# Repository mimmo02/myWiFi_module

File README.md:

# myWiFi_module

Generic WiFi pcb based on ESP12E module, with 6 output and 3 input.
Appropriate to develope IoT application.

## Authors

- [@Domenico Aquilino](https://github.com/mimmo02)

## Hardware

The IO are customizable, in this case the configuration is made such as there are 6 output and 3 input.

#### Mounted components:

| Component | Type     | Module ESP12E |
| :-------- | :------- | :------------------------- |
| `R6 & R13` | input | `GPIO16` |
| `R7 & R14` | input | `GPIO14` |
| `R8 & R15` | input | `GPIO12` |
| `Q4` | output | `GPIO13` |
| `Q5` | output | `GPIO15` |
| `Q6` | output | `GPIO02` |
| `Q7` | output | `GPIO00` |
| `Q8` | output | `GPIO04` |
| `Q9` | output | `GPIO05` |

#### PCB PIN:

alimentation jumper
| Connector | Pin     | Description |
| :-------- | :------ | :---------- |
| **JP1** | `1-4` | 24V |
| **JP1** | `2-5` | 5V |
| **JP1** | `3-6` | 3.3V |

alimentation connector
| Connector | Pin     | Description |
| :-------- | :------ | :---------- |
| **X1** | `1` | GND |
| **X1** | `2` | +24V |
| **X1** | `3` | +5V |
| **X1** | `4` | +3.3V |

programmation connector
| Connector | Pin     | Description |
| :-------- | :------ | :---------- |
| **X3** | `1` | Rx |
| **X3** | `2` | Tx |
| **X3** | `3` | GND |

GPIO connector
| Connector | Pin     | ESP12E |  esp8266 |
| :-------- | :------ | :---------- | :-----|
| **X2** | `1` | GND | GND |
| **X2** | `2` | GPIO16 | GPIO16 |
| **X2** | `3` | GPIO14 | GPIO14 |
| **X2** | `4` | GPIO12 | GPIO12 |
| **X2** | `5` | GPIO13 | GPIO13 |
| **X2** | `6` | GPIO15 | GPIO15 |
| **X2** | `7` | GPIO02 | GPIO02 |
| **X2** | `8` | GPIO00 | GPIO00 |
| **X2** | `9` | GPIO04 | GPIO04 |
| **X2** | `10` | GPIO05 | GPIO05 |
| **X2** | `11` | ADC | ADC |

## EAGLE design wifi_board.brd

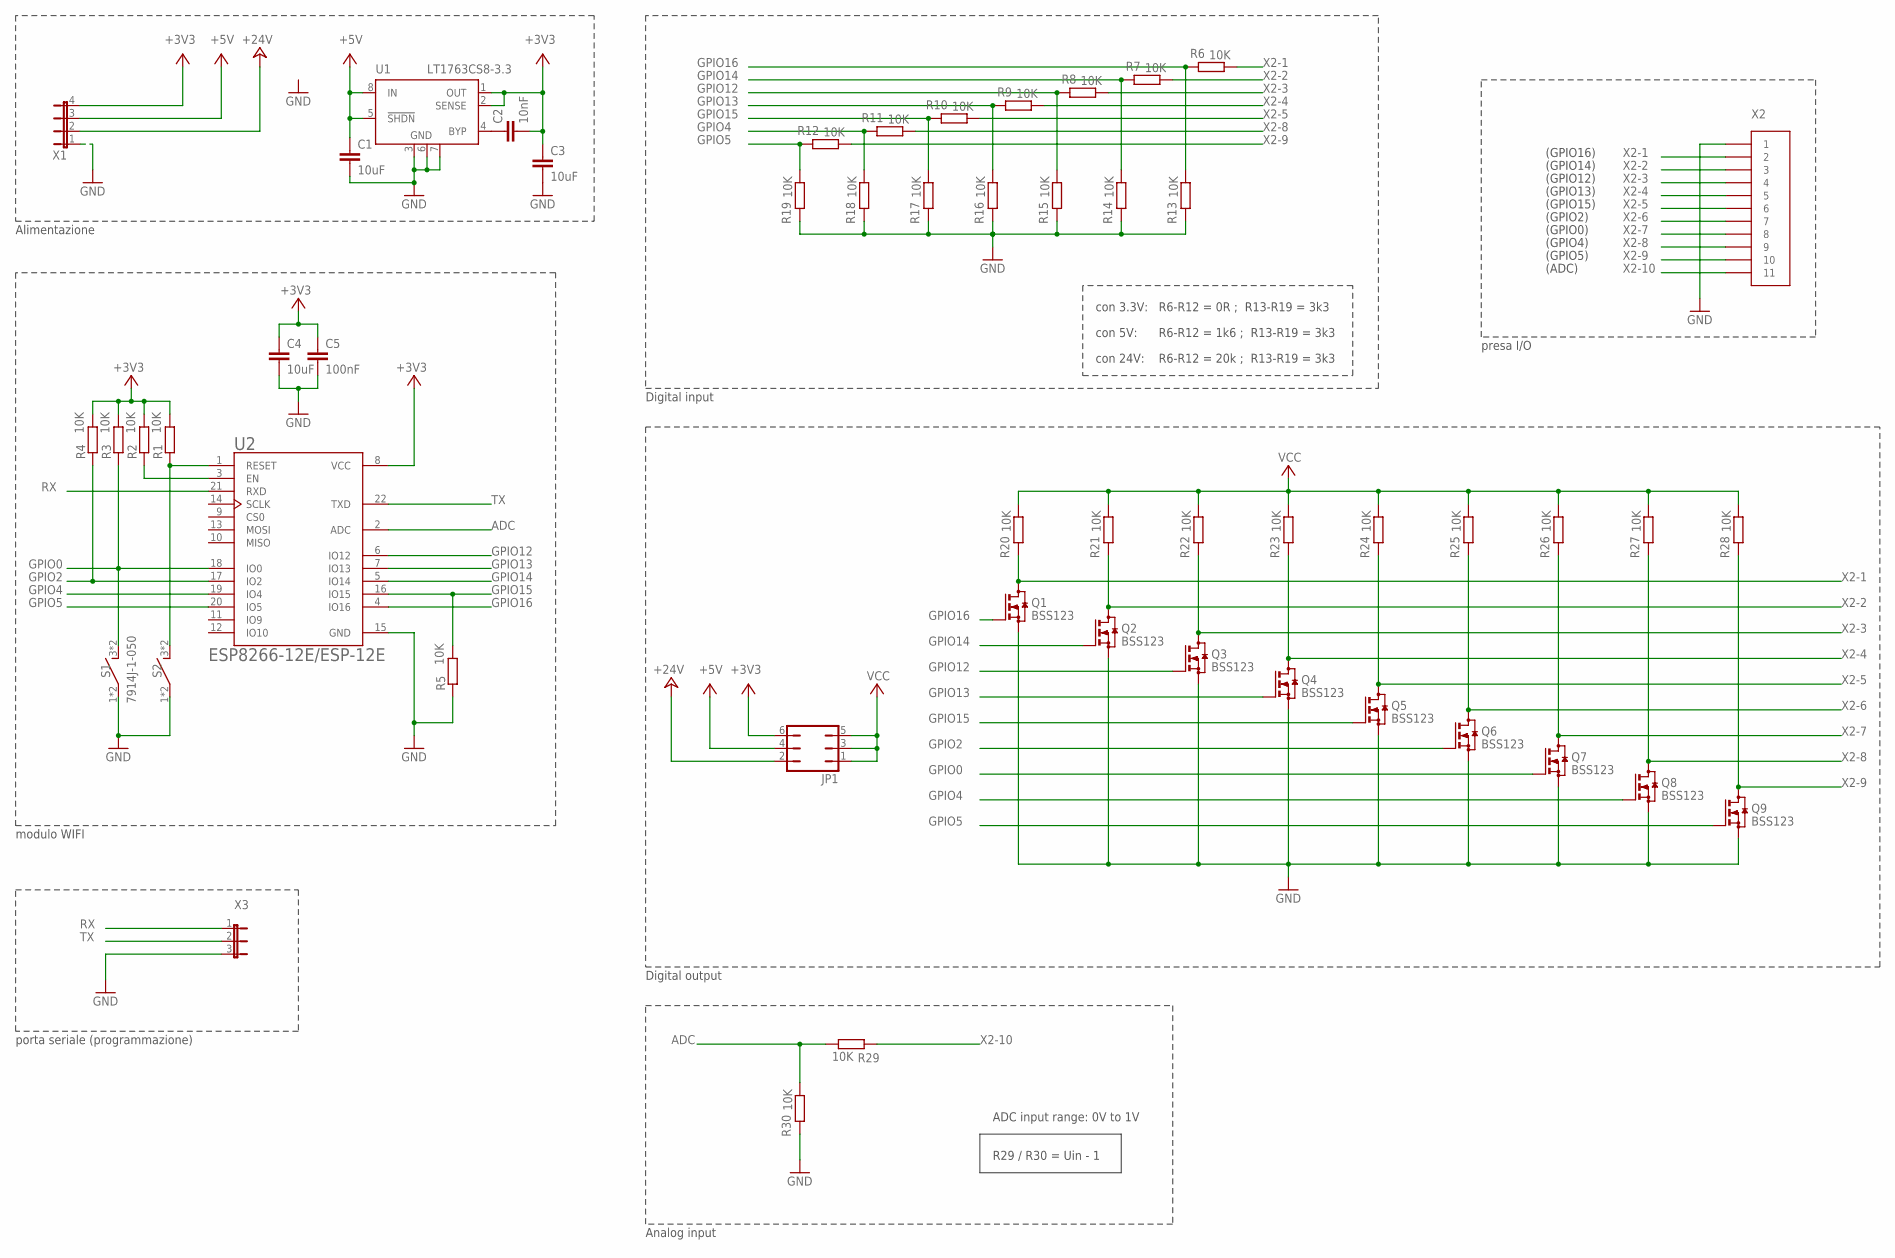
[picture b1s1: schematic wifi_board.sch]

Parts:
C1, C3, C4: 10uF; C0805
C2: 10nF; C0805
C5: 100nF; C0805
JP1: JP3Q
Q1, Q2, Q3, Q4, Q5, Q6, Q7, Q8, Q9: BSS123; SOT23
R1, R2, R3, R4, R5, R6, R7, R8, R9, R10, R11, R12, R13, R14, R15, R16, R17, R18, R19, R20, R21, R22, R23, R24, R25, R26, R27, R28, R29, R30: 10K; R0805
S1, S2: 7914J-1-050; 7914J1000E
U1: LT1763CS8-3.3; SOIC8
U2: ESP8266-12E/ESP-12E; XCVR_ESP8266-12E/ESP-12E
X1: JP4E; JP4
X2: X11P
X3: JP2E; JP2

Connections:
+3V3: C2.2, C3.1, C4.1, C5.1, JP1.6, R1.2, R2.2, R3.2, R4.2, U1.1 (OUT), U1.2 (SENSE), U2.8 (VCC), X1.4
+5V: C1.1, JP1.4, U1.5 (!SHDN), U1.8 (IN), X1.3
+24V: JP1.2, X1.2
ADC: R29.1, R30.1, U2.2 (ADC)
GND: C1.2, C3.2, C4.2, C5.2, Q1.2 (S), Q2.2 (S), Q3.2 (S), Q4.2 (S), Q5.2 (S), Q6.2 (S), Q7.2 (S), Q8.2 (S), Q9.2 (S), R5.1, R13.2, R14.2, R15.2, R16.2, R17.2, R18.2, R19.2, R30.2, S1.1, S1.2 (1), S2.1, S2.2 (1), U1.3 (GND), U1.6 (GND), U1.7 (GND), U2.15 (GND), X1.1, X2.1, X3.3
GPIO0: Q7.1 (G), R3.1, S1.3 (2), S1.4 (2), U2.18 (IO0)
GPIO2: Q6.1 (G), R4.1, U2.17 (IO2)
GPIO4: Q8.1 (G), R11.2, R18.1, U2.19 (IO4)
GPIO5: Q9.1 (G), R12.2, R19.1, U2.20 (IO5)
GPIO12: Q3.1 (G), R8.2, R15.1, U2.6 (IO12)
GPIO13: Q4.1 (G), R9.2, R16.1, U2.7 (IO13)
GPIO14: Q2.1 (G), R7.2, R14.1, U2.5 (IO14)
GPIO15: Q5.1 (G), R5.2, R10.2, R17.1, U2.16 (IO15)
GPIO16: Q1.1 (G), R6.2, R13.1, U2.4 (IO16)
unnamed: R1.1, S2.3 (2), S2.4 (2), U2.1 (RESET)
unnamed: R2.1, U2.3 (EN)
unnamed: C2.1, U1.4 (BYP)
RX: U2.21 (RXD), X3.1
TX: U2.22 (TXD), X3.2
VCC: JP1.1, JP1.3, JP1.5, R20.1, R21.1, R22.1, R23.1, R24.1, R25.1, R26.1, R27.1, R28.1
X2-1: Q1.3 (D), R6.1, R20.2, X2.2
X2-2: Q2.3 (D), R7.1, R21.2, X2.3
X2-3: Q3.3 (D), R8.1, R22.2, X2.4
X2-4: Q4.3 (D), R9.1, R23.2, X2.5
X2-5: Q5.3 (D), R10.1, R24.2, X2.6
X2-6: Q6.3 (D), R25.2, X2.7
X2-7: Q7.3 (D), R26.2, X2.8
X2-8: Q8.3 (D), R11.1, R27.2, X2.9
X2-9: Q9.3 (D), R12.1, R28.2, X2.10
X2-10: R29.2, X2.11

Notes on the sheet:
Alimentazione
modulo WIFI
con 3.3V: R6-R12 = 0R ; R13-R19 = 3k3
con 5V: R6-R12 = 1k6 ; R13-R19 = 3k3
con 24V: R6-R12 = 20k ; R13-R19 = 3k3
Digital input
Digital output
porta seriale (programmazione)
presa I/O
ADC input range: 0V to 1V
R29 / R30 = Uin - 1
Analog input
(GPIO16)
(GPIO14)
(GPIO12)
(GPIO13)
(GPIO15)
(GPIO2)
(GPIO0)
(GPIO4)
(GPIO5)
(ADC)

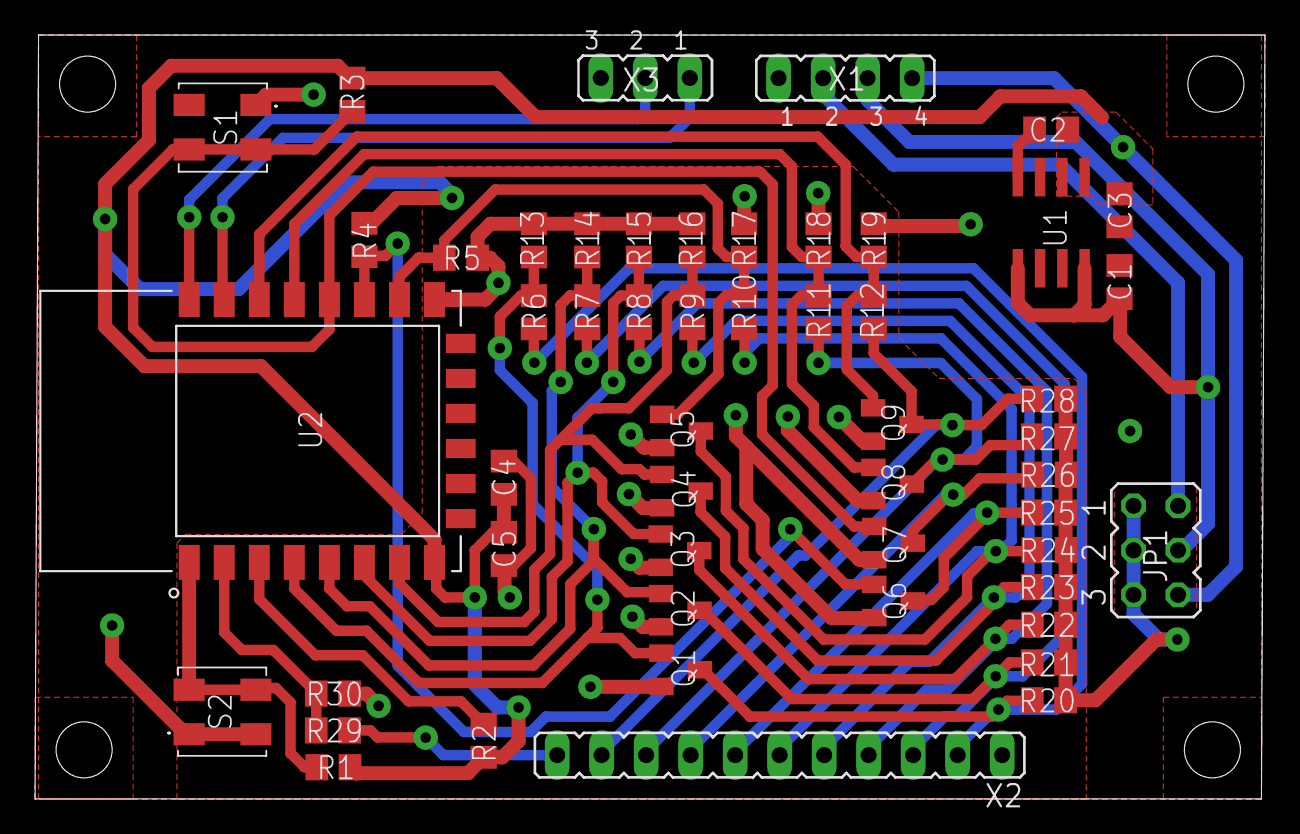
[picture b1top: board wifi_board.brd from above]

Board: 2 copper layers, 70.2 x 43.6 mm, 52 parts (0 on the bottom side), 30 nets.

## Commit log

2024-02-06 Rename ota-basic.ino to myWiFi.ino
